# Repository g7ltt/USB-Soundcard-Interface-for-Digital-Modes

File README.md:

# USB Soundcard Interface for Digital Modes

All-in-one interface for ham radio digital modes. Includes a USB sound card for simpler wiring. Uses VOX for PTT.

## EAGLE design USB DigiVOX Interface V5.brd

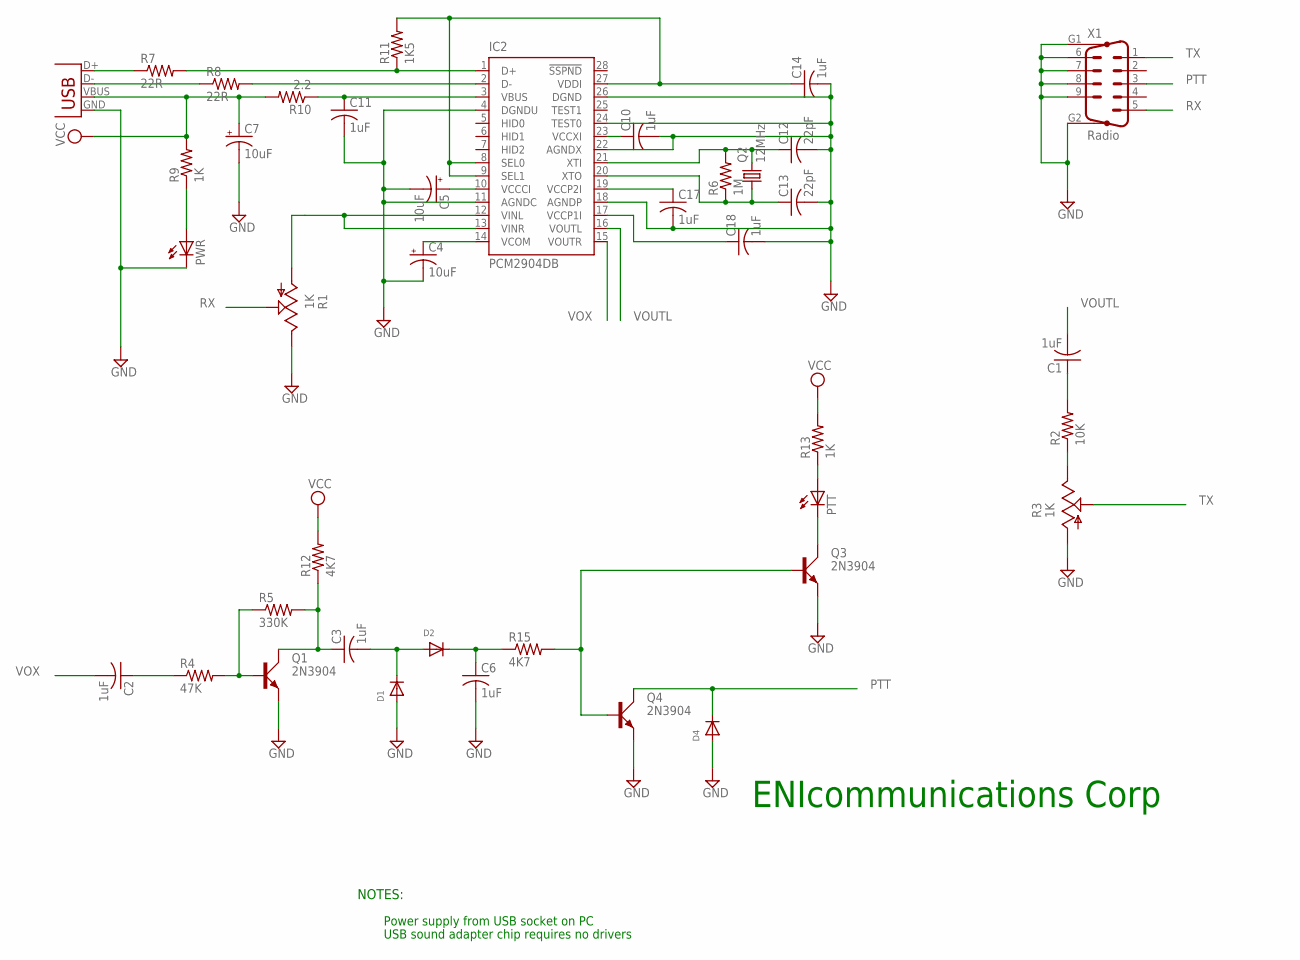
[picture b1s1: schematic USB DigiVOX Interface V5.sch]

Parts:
C1, C2, C3, C6, C10, C11, C14, C17, C18: 1uF; C025-025X050
C4, C5, C7: 10uF; CPOL-RADIAL-10UF-25V
C12, C13: 22pF; C025-025X050
D1, D2, D4: DIODEDO-1N4148; DO-1N4148
IC2: PCM2904DB; SSOP28DB
PTT: LED3MM
PWR: LED3MM
Q1, Q3, Q4: 2N3904; TO92D
Q2: 12MHz; HC49/S
R1, R3: 1K; CA6V
R2: 10K; 0204/7
R4: 47K; 0207/2V
R5: 330K; 0207/2V
R6: 1M; 0207/2V
R7, R8: 22R; 0207/2V
R9: 1K; 0207/2V
R10: 2.2; 0207/2V
R11: 1K5; 0207/2V
R12, R15: 4K7; 0207/2V
R13: 1K; 0204/7
X1: Radio; M09HP
X2: USBSMD; USB-MINIB

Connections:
GND: C4.2 (-), C5.2 (-), C6.2, C7.2 (-), C10.2, C11.2, C12.2, C13.2, C14.2, C17.2, C18.2, D1.A, D4.A, IC2.4 (DGNDU), IC2.11 (AGNDC), IC2.18 (AGNDP), IC2.22 (AGNDX), IC2.24 (TEST0), IC2.26 (DGND), PWR.K (C), Q1.E, Q3.E, Q4.E, R1.E, R3.A, X1.6, X1.7, X1.8, X1.9, X1.G1, X1.G2, X2.GND
unnamed: C1.1, R2.2
unnamed: R2.1, R3.E
unnamed: C5.1 (+), IC2.10 (VCCCI)
unnamed: C12.1, IC2.21 (XTI), Q2.2, R6.2
unnamed: PWR.A, R9.1
unnamed: C13.1, IC2.20 (XTO), Q2.1, R6.1
unnamed: C10.1, IC2.23 (VCCXI)
unnamed: C2.1, R4.1
unnamed: C4.1 (+), IC2.14 (VCOM)
unnamed: Q1.B, R4.2, R5.1
unnamed: C3.1, Q1.C, R5.2, R12.1
unnamed: C3.2, D1.C, D2.A
unnamed: C14.1, IC2.8 (SEL0), IC2.9 (SEL1), IC2.27 (VDDI), R11.2
unnamed: C6.1, D2.C, R15.1
unnamed: C11.1, IC2.3 (VBUS), R10.1
unnamed: Q3.B, Q4.B, R15.2
unnamed: R7.1, X2.D+
unnamed: C17.1, IC2.19 (VCCP2I)
unnamed: IC2.1 (D+), R7.2, R11.1
unnamed: IC2.2 (D-), R8.2
unnamed: PTT.K (C), Q3.C
unnamed: R8.1, X2.D-
unnamed: PTT.A, R13.1
unnamed: C18.1, IC2.17 (VCCP1I)
PTT: D4.C, Q4.C, X1.3
RX: R1.S, X1.5
TX: R3.S, X1.1
VCC: C7.1 (+), R9.2, R10.2, R12.2, R13.2, X2.VBUS
VINL: IC2.12 (VINL), IC2.13 (VINR), R1.A
VOUTL: C1.2, IC2.16 (VOUTL)
VOX: C2.2, IC2.15 (VOUTR)

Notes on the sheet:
NOTES:
Power supply from USB socket on PC
USB sound adapter chip requires no drivers
ENIcommunications Corp

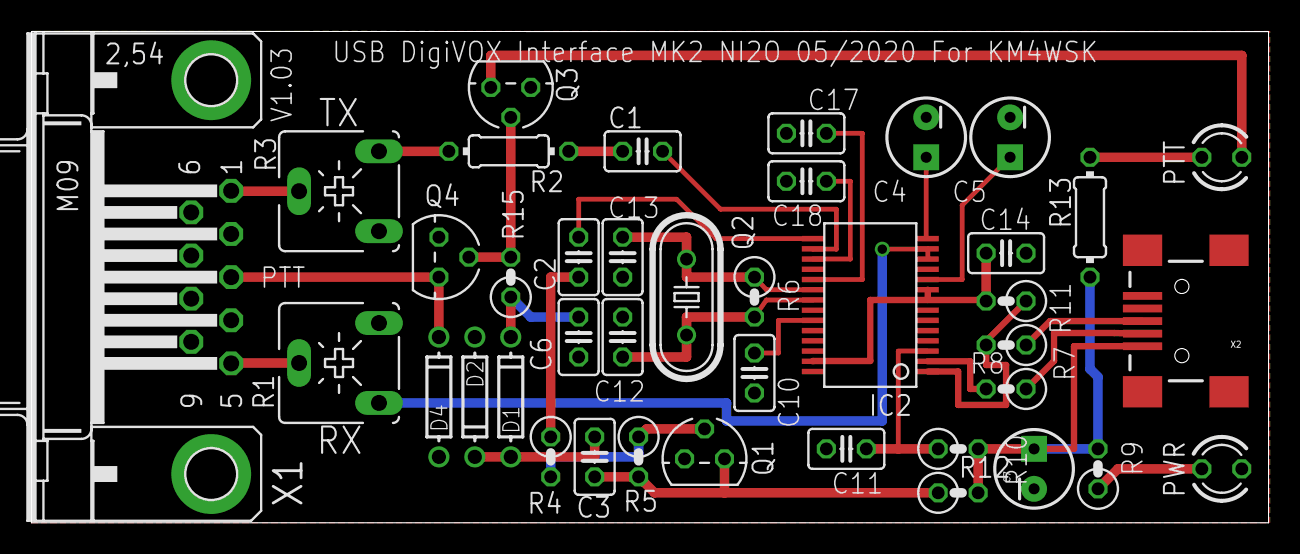
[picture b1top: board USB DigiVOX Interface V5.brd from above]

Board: 2 copper layers, 78.7 x 31.2 mm, 40 parts (0 on the bottom side), 32 nets.

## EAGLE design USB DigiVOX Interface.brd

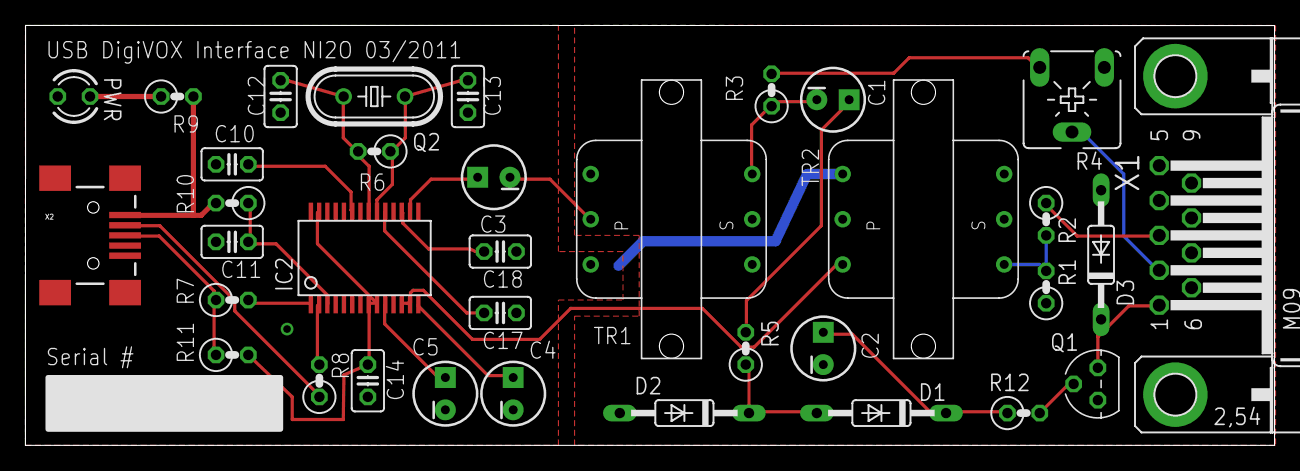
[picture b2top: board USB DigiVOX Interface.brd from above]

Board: 2 copper layers, 98.2 x 33.0 mm, 35 parts (0 on the bottom side), 30 nets.

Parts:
C1, C2, C4, C5: 10uF; CPOL-RADIAL-10UF-25V
C3: 4.7uF; CPOL-RADIAL-10UF-25V
C10, C11, C14, C17, C18: 1uF; C025-025X050
C12, C13: 22pF; C025-025X050
D1, D2, D3: 1N4148; DO35-10
IC2: PCM2904DB; SSOP28DB
PWR: LED3MM
Q1: 2N3904; TO92
Q2: 12MHz; HC49/S
R1: 680R; 0207/2V
R2: 10K; 0207/2V
R3, R5: 4k7; 0207/2V
R4: 1K; CA6V
R6: 1M; 0207/2V
R7, R8: 22R; 0207/2V
R9: 1K; 0207/2V
R10: 2.2; 0207/2V
R11: 1K5; 0207/2V
R12: 2k2; 0207/2V
TR1, TR2: 42TM016; 42TM
X1: M09HP
X2: USBSMD; USB-MINIB

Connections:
GND: C4.2, C5.2, C10.2, C11.2, C12.2, C13.2, C14.2, C17.2, C18.2, IC2.4, IC2.11, IC2.18, IC2.22, IC2.24, IC2.26, PWR.K, TR1.3, TR2.1, X2.GND
GNDA: C2.2, D2.A, D3.A, Q1.3, R1.1, R4.A, TR1.4, TR2.6, X1.5, X1.G1, X1.G2
INPUT: IC2.12, IC2.13, TR2.3
unnamed: C3.1, IC2.16
unnamed: C1.2, R3.1, TR1.6
unnamed: C5.1, IC2.10
unnamed: C12.1, IC2.21, Q2.2, R6.2
unnamed: PWR.A, R9.1
unnamed: C13.1, IC2.20, Q2.1, R6.1
unnamed: C10.1, IC2.23
unnamed: R1.2, R2.2, TR2.4
unnamed: C4.1, IC2.14
unnamed: C1.1, R5.2
unnamed: D1.A, D2.C, R5.1
unnamed: C14.1, IC2.8, IC2.9, IC2.27, R11.2
unnamed: C3.2, TR1.2
unnamed: C11.1, IC2.3, R10.1
unnamed: Q1.2, R12.2
unnamed: R3.2, R4.E
unnamed: C17.1, IC2.19
unnamed: R7.1, R11.1, X2.D+
unnamed: IC2.2, R8.2
unnamed: IC2.1, R7.2
unnamed: R8.1, X2.D-
unnamed: C2.1, D1.C, R12.1
unnamed: C18.1, IC2.17
PTT: D3.C, Q1.1, X1.1
RX: R2.1, X1.3
TX: R4.S, X1.2
VCC: R9.2, R10.2, X2.VBUS

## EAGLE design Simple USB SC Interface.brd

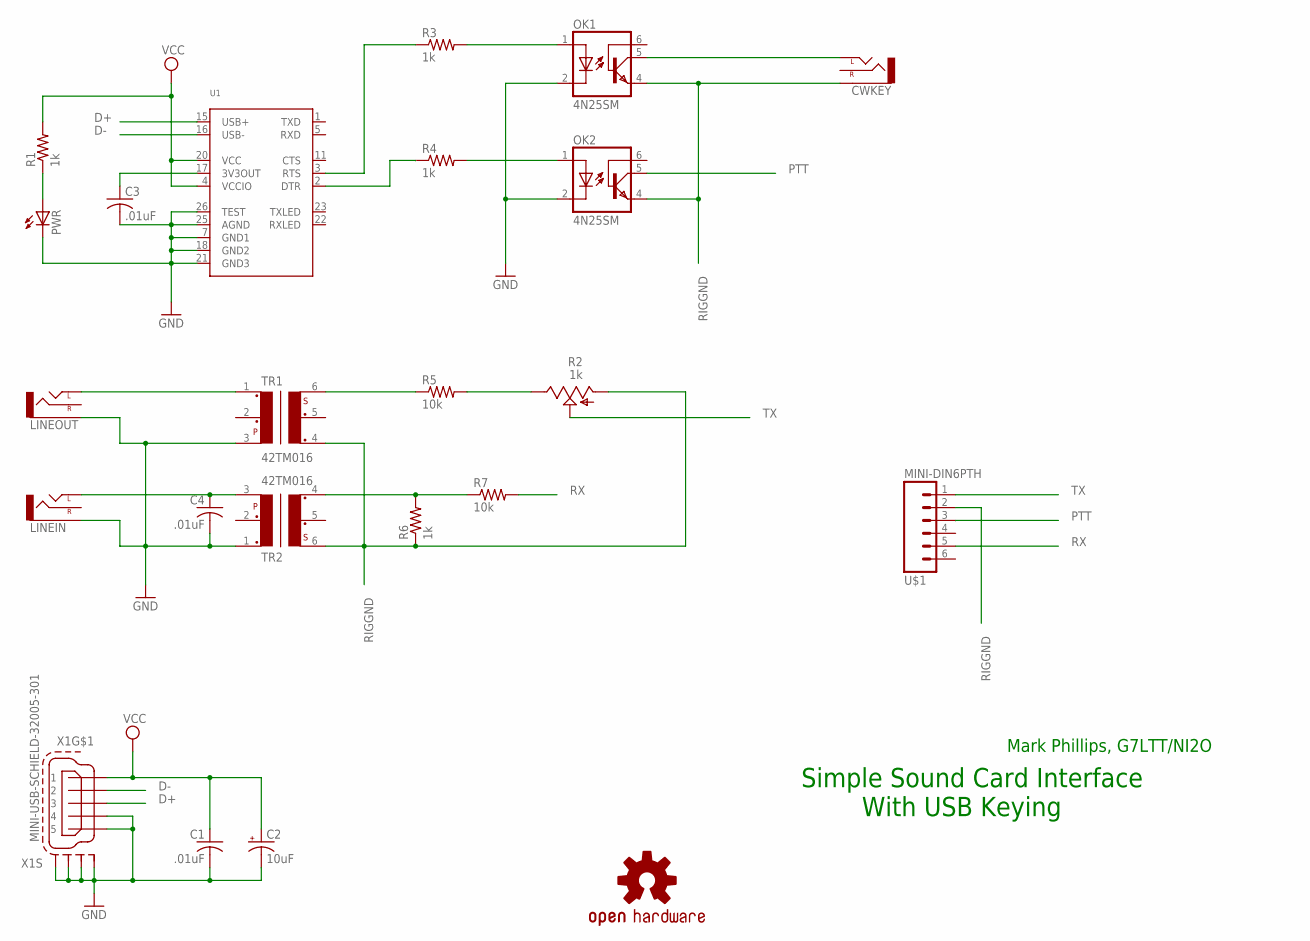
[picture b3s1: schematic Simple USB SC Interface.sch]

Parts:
C1, C3, C4: .01uF; C0805
C2: 10uF; E2,5-5
CWKEY: AUDIO-JACKSMD2; AUDIO-JACK-3.5MM-SMD
LINEIN: AUDIO-JACKSMD2; AUDIO-JACK-3.5MM-SMD
LINEOUT: AUDIO-JACKSMD2; AUDIO-JACK-3.5MM-SMD
LOGO1: OSHW-LOGOM; OSHW-LOGO-M
OK1, OK2: 4N25SM; DIL6-SMD
PWR: LEDCHIP-LED0805; CHIP-LED0805
R1, R3, R4, R6: 1k; M0805
R2: 1k; CA6V
R5, R7: 10k; M0805
TR1, TR2: 42TM016; 42TM
U1: FT232RLSSOP28; SSOP28DB
U$1: MINI-DIN6PTH; MINI-DIN6
X1: MINI-USB-SCHIELD-32005-301; 32005-301

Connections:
CWKEY: CWKEY.TIP (LEFT), OK1.5 (COL)
D+: U1.15 (USB+), X1.3
D-: U1.16 (USB-), X1.2
GND: C1.2, C2.-, C3.2, C4.2, LINEIN.SLEEVE, LINEOUT.SLEEVE, OK1.2 (C), OK2.2 (C), PWR.C, TR1.3, TR2.1, U1.7 (GND1), U1.18 (GND2), U1.21 (GND3), U1.25 (AGND), U1.26 (TEST), X1.4, X1.5, X1.M1 (S1), X1.M2 (S2), X1.M3 (S3), X1.M4 (S4)
unnamed: PWR.A, R1.1
unnamed: OK1.1 (A), R3.2
unnamed: C3.1, U1.17 (3V3OUT)
unnamed: OK2.1 (A), R4.2
unnamed: R3.1, U1.3 (RTS)
unnamed: R4.1, U1.2 (DTR)
unnamed: C4.1, LINEIN.TIP (LEFT), TR2.3
unnamed: LINEOUT.TIP (LEFT), TR1.1
unnamed: R5.1, TR1.6
unnamed: R2.E, R5.2
unnamed: R6.2, R7.1, TR2.4
PTT: OK2.5 (COL), U$1.3
RIGGND: CWKEY.SLEEVE, OK1.4 (EMI), OK2.4 (EMI), R2.A, R6.1, TR1.4, TR2.6, U$1.2
RX: R7.2, U$1.5
TX: R2.S, U$1.1
VCC: C1.1, C2.+, R1.2, U1.4 (VCCIO), U1.20 (VCC), X1.1

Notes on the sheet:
Simple Sound Card Interface With USB Keying
Mark Phillips, G7LTT/NI2O

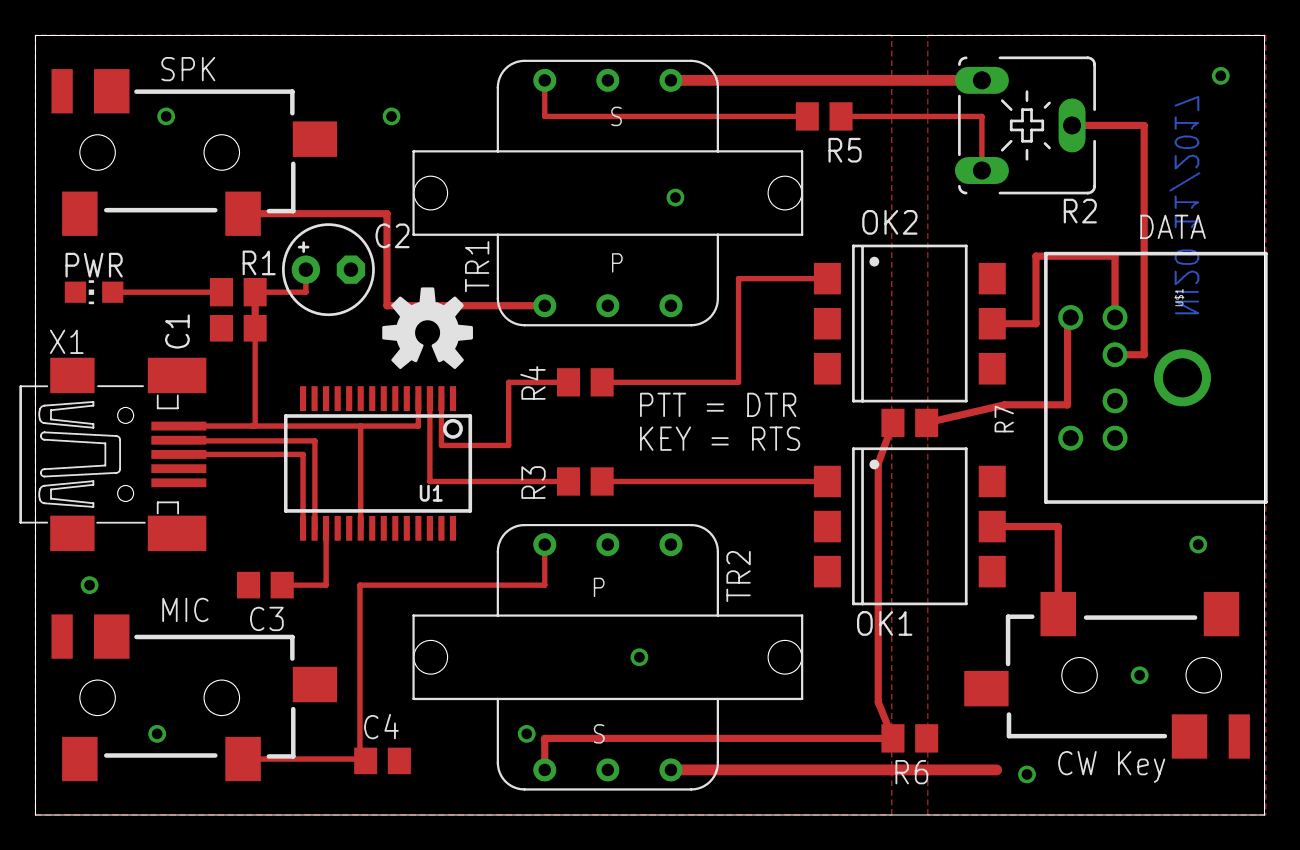
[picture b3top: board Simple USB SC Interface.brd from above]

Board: 2 copper layers, 69.3 x 43.9 mm, 23 parts (0 on the bottom side), 20 nets.

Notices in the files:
parts and their libraries:
SparkFun-Aesthetics: Licensing: CC v3.0 Share-Alike You are welcome to use this library for commercial purposes.
microbuilder: This work is placed in the public domain, and may be freely used for commercial and non-commercial work with the following conditions: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
